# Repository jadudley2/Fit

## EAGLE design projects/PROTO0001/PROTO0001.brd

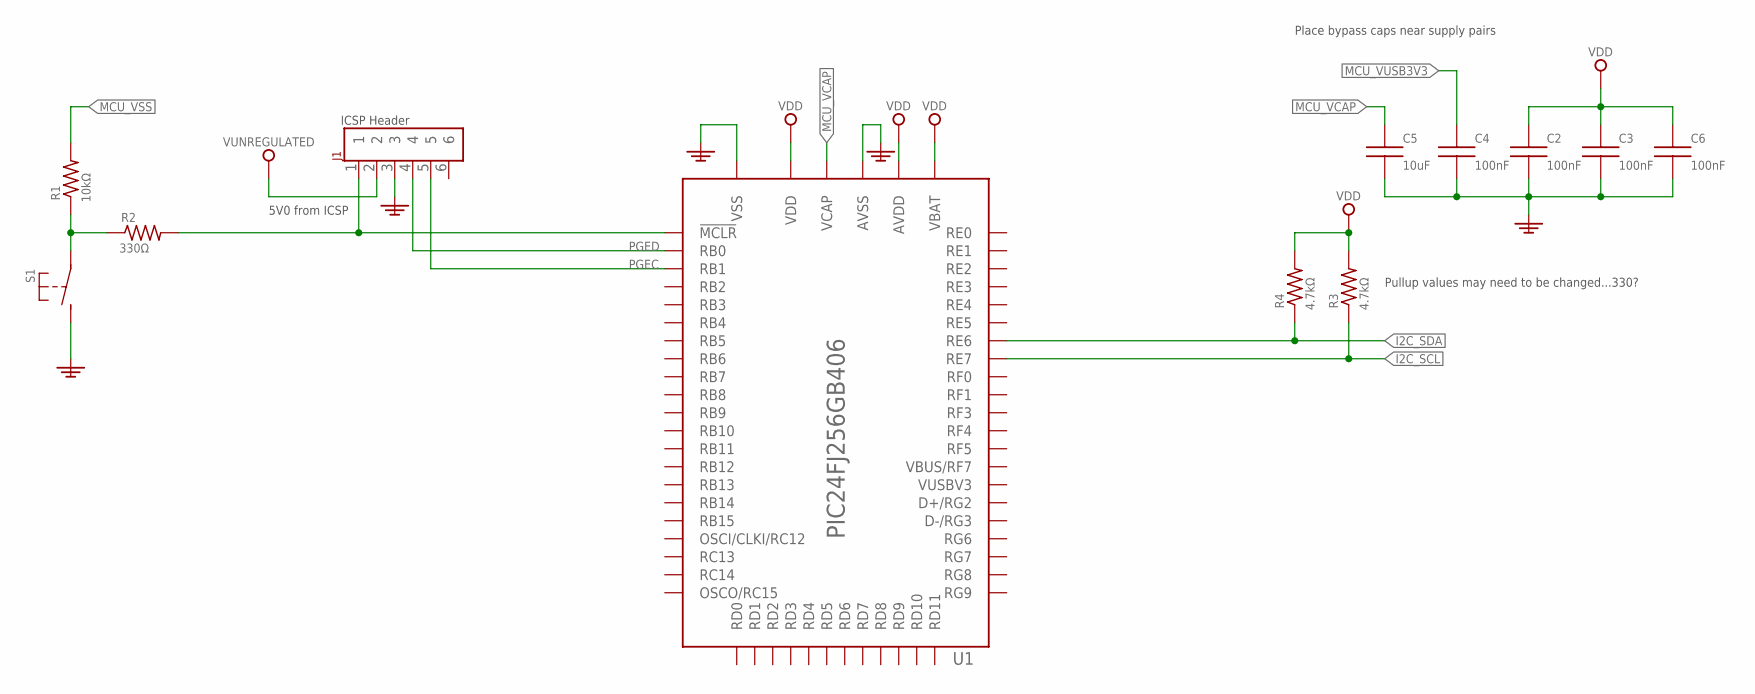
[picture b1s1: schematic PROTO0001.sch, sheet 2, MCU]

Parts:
C2, C3, C4, C6: CAP_100N_0402_CERAMIC; CAPACITOR_0402
C5: CAP_10U_0805_CERAMIC; CAPACITOR_0805
J1: HEADER_2.54MM_1X6
R1: 10.0kOhm; RESISTOR_0402
R2: RES_330_0402; RESISTOR_0402
R3, R4: RES_4.7K_0402; RESISTOR_0402
S1: SWITCH_TACTILE_THRU
U1: PIC24FJ256GB406; QFP50P1200X1200X120-64L30

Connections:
5V0: C2.1, C3.1, C6.1, R3.2, R4.2, U1.10 (VDD), U1.19 (AVDD), U1.26 (VDD), U1.38 (VDD), U1.57 (VBAT); also elsewhere on the board
GND: C2.2, C3.2, C4.2, C5.2, C6.2, J1.3, S1.3 (S), S1.4 (S), U1.9 (VSS), U1.20 (AVSS), U1.25 (VSS), U1.41 (VSS); also elsewhere on the board
I2C_SCL: R3.1, U1.3 (RE7); also elsewhere on the board
I2C_SDA: R4.1, U1.2 (RE6); also elsewhere on the board
MCU_VCAP: C5.1, U1.56 (VCAP)
MCU_VSS: R1.2
MCU_VUSB3V3: C4.1
unnamed: J1.1, R2.2, U1.7 (!MCLR)
unnamed: R1.1, R2.1, S1.1, S1.2
PGEC: J1.5, U1.15 (RB1)
PGED: J1.4, U1.16 (RB0)
VUNREGULATED: J1.2

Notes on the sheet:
Place bypass caps near supply pairs
5V0 from ICSP
ICSP Header
Pullup values may need to be changed...330?

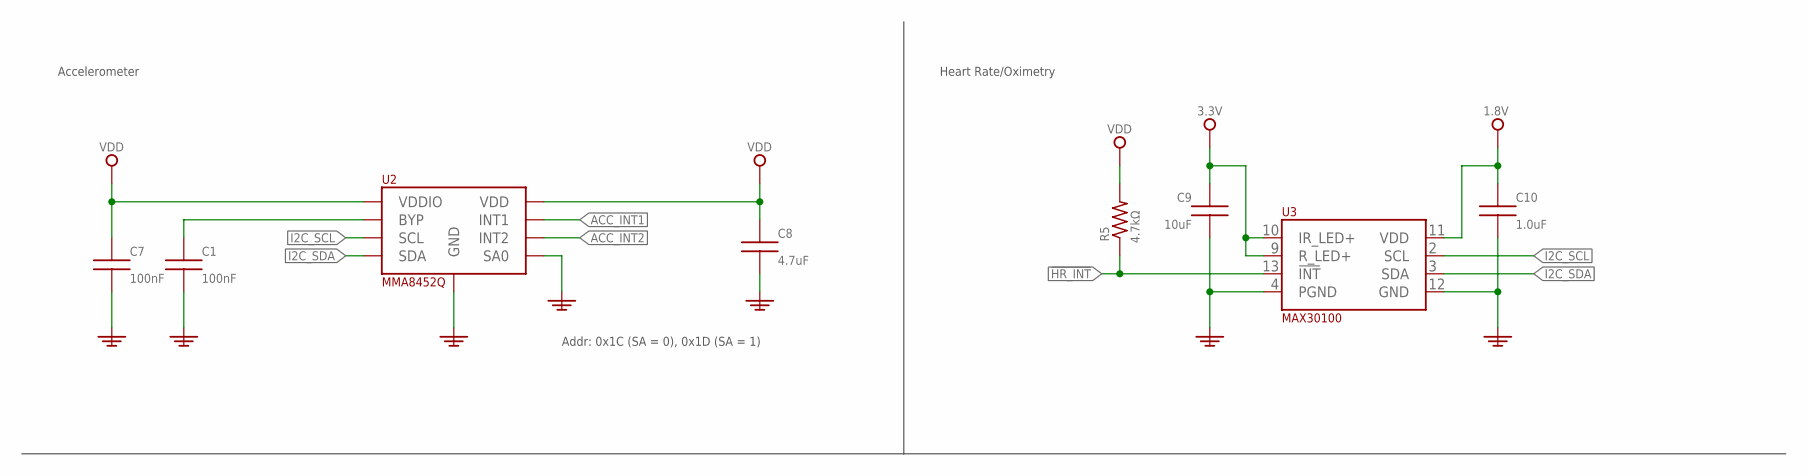
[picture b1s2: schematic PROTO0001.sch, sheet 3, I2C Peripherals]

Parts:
C1, C7: CAP_100N_0402_CERAMIC; CAPACITOR_0402
C8: CAP_4.7U_0603_CERAMIC; CAPACITOR_0603
C9: CAP_10U_0805_CERAMIC; CAPACITOR_0805
C10: CAP_1U_0603_CERAMIC; CAPACITOR_0603
R5: RES_4.7K_0402; RESISTOR_0402
U2: MMA8452Q; QFN50P300X300X100-16
U3: MAX30100; 21-0880

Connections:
1V8: C10.1, U3.11 (VDD)
3V3: C9.1, U3.9 (R_LED+), U3.10 (IR_LED+)
5V0: C7.1, C8.1, R5.2, U2.1 (VDDIO), U2.14 (VDD); also elsewhere on the board
!HR_INT: R5.1, U3.13 (!INT)
ACC_INT1: U2.11 (INT1)
ACC_INT2: U2.9 (INT2)
GND: C1.2, C7.2, C8.2, C9.2, C10.2, U2.5 (GND), U2.7 (SA0), U2.12 (GND), U3.4 (PGND), U3.12 (GND); also elsewhere on the board
I2C_SCL: U2.4 (SCL), U3.2 (SCL); also elsewhere on the board
I2C_SDA: U2.6 (SDA), U3.3 (SDA); also elsewhere on the board
unnamed: C1.1, U2.2 (BYP)

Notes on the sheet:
Addr: 0x1C (SA = 0), 0x1D (SA = 1)
Accelerometer
Heart Rate/Oximetry

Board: 2 copper layers, 20 parts (0 on the bottom side), 13 nets, no tracks yet.

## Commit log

2016-09-13 Adding initial schematic, library, datasheets etc. Initial chips chosen for Accelerometer, HR/Oximeter, MCU, Temperature (x2), with an eye towards power consumption and standby/sleep mode, communicat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
2016-09-15 Added i2c peripherals (accelerometer and HR/oximeter)
